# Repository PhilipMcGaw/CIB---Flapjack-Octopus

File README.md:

# CIB - Flapjack Octopus
<div align="center">

<!-- removed as not used in this repo  -->

</div>

|  | Breakout board for Labjack T7 |
| ------------- |:-------------:|

Breakout board for Labjack T7

### Flapjack Octopus -- Labjack T7 Breakout

This is a breakout PCB for a Labjack T7, with 2.5 mm pitch screw headers to allow for quick wiring to the breakout PCB.

  * Digital IO ports are 5 V tolerant, there is no additional protection on the PCB.
  * Digital IO on ports C, E, F and M each have an LED that illuminates when 5V DC is applied
  * Digital IO port F is also set up as eight relay outputs, allowing up to eight 12/24 V (separate power supply required) to be driven from the T7 Labjack
  * Analogue in ports are taken via a potential divider to allow pre-scaling if required.
  * Additional terminals are available for 5V and Ground, as well as other pins, these are on the lower edge.

# Sub Modules

github.com/PhilipMcGaw/common_kicad

git submodule add https://github.com/PhilipMcGaw/common_kicad KiCAD/Common

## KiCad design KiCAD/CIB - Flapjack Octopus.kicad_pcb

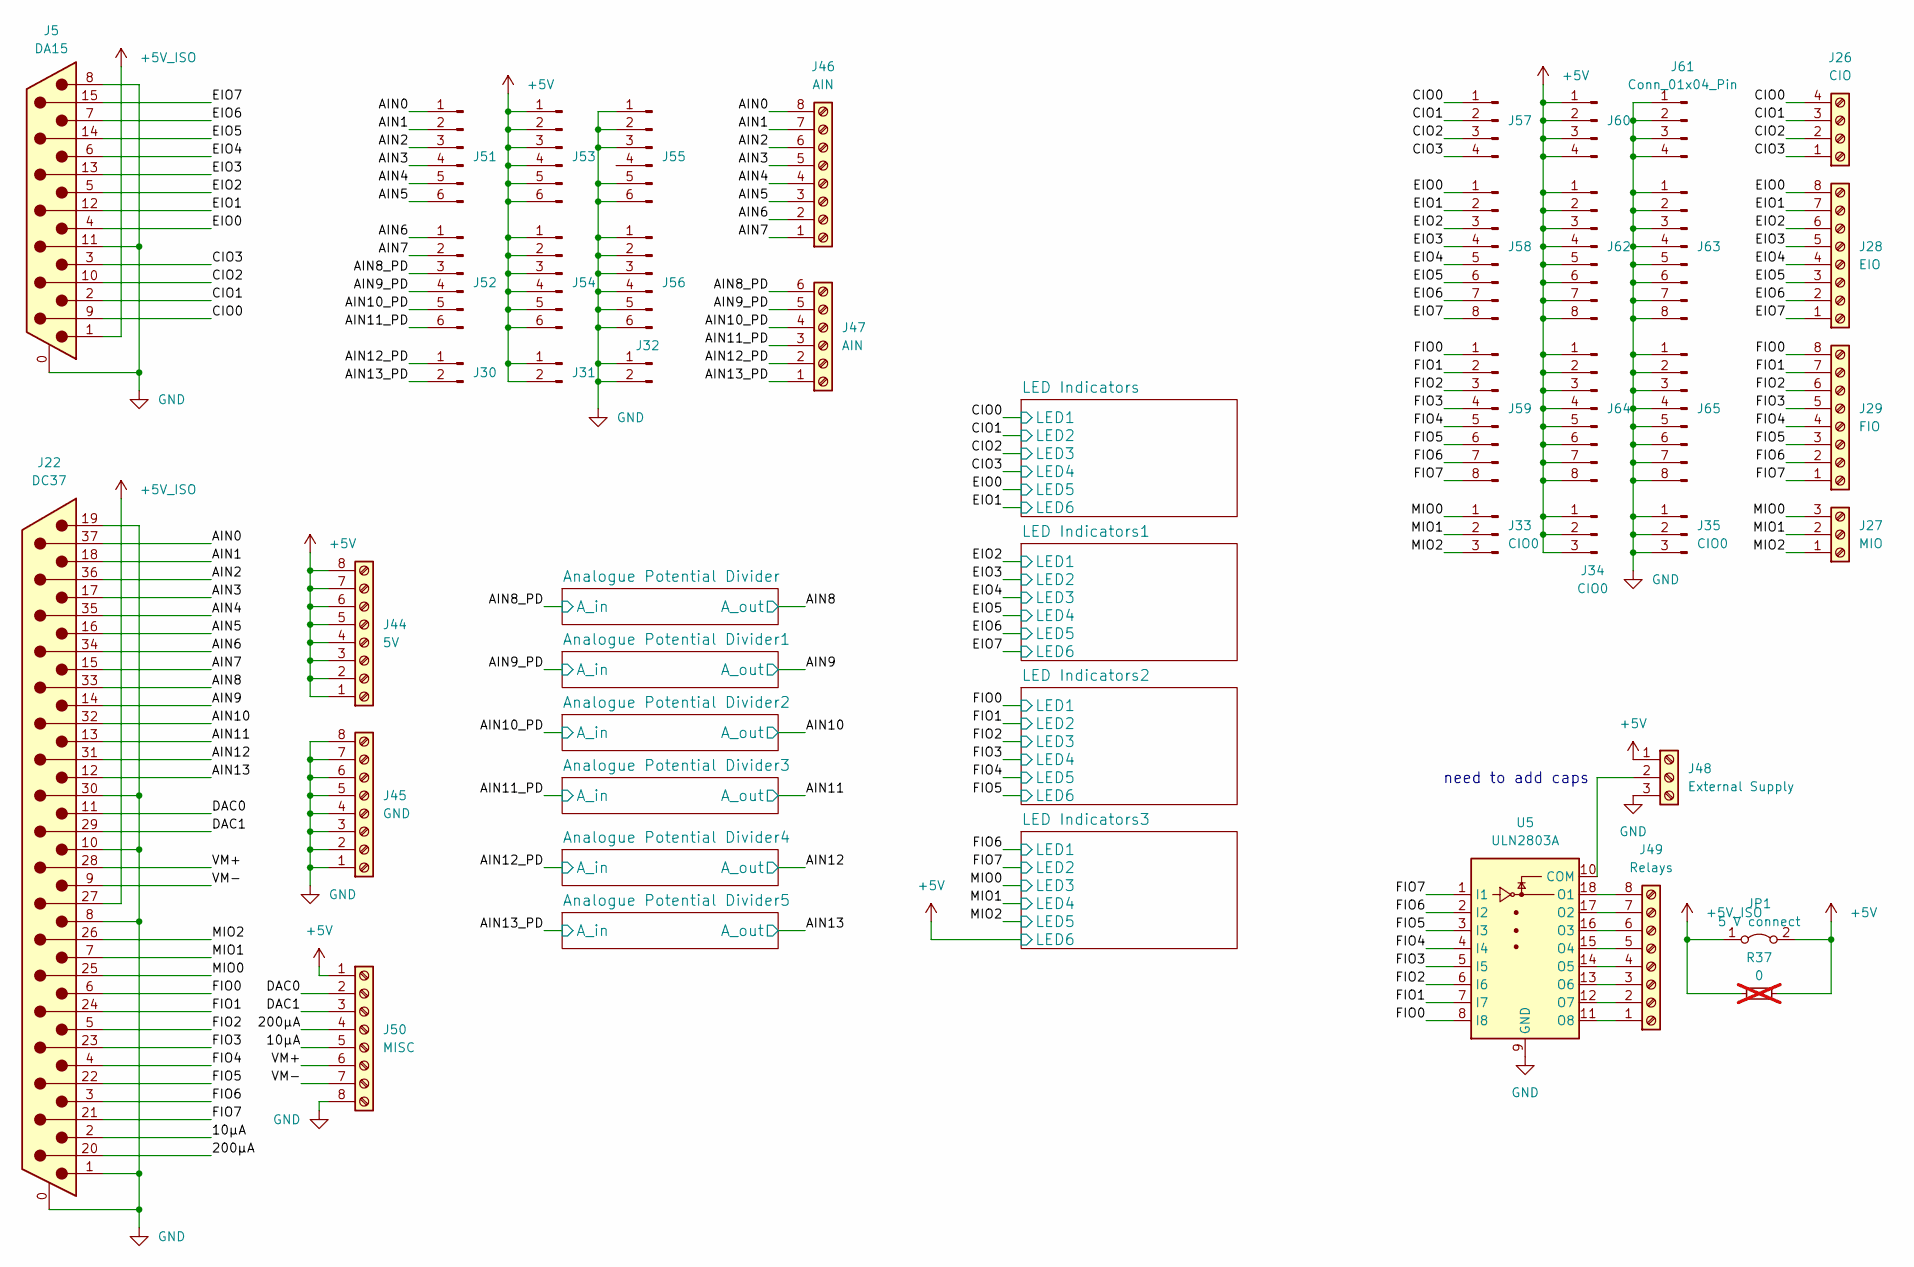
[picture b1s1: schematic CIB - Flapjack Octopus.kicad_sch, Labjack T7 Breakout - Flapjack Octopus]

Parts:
J5: DA15; DSUB-15_Male_Horizontal_P2.77x2.84mm_EdgePinOffset9.90mm_Ho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
J22: DC37; DSUB-37_Male_Horizontal_P2.77x2.84mm_EdgePinOffset7.70mm_Ho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
J26: CIO; TerminalBlock_Phoenix_MPT-0,5-4-2.54_1x04_P2.54mm_Horizontal
J27: MIO; TerminalBlock_Phoenix_MPT-0,5-3-2.54_1x03_P2.54mm_Horizontal
J28: EIO; TerminalBlock_Phoenix_MPT-0,5-8-2.54_1x08_P2.54mm_Horizontal
J29: FIO; TerminalBlock_Phoenix_MPT-0,5-8-2.54_1x08_P2.54mm_Horizontal
J30, J31, J32: Conn_01x02_Pin; PinSocket_1x02_P2.54mm_Vertical
J33, J34, J35: CIO0; PinSocket_1x03_P2.54mm_Vertical
J44: 5V; TerminalBlock_Phoenix_MPT-0,5-8-2.54_1x08_P2.54mm_Horizontal
J45: GND; TerminalBlock_Phoenix_MPT-0,5-8-2.54_1x08_P2.54mm_Horizontal
J46: AIN; TerminalBlock_Phoenix_MPT-0,5-8-2.54_1x08_P2.54mm_Horizontal
J47: AIN; TerminalBlock_Phoenix_MPT-0,5-6-2.54_1x06_P2.54mm_Horizontal
J48: External Supply; TerminalBlock_Phoenix_MPT-0,5-3-2.54_1x03_P2.54mm_Horizontal
J49: Relays; TerminalBlock_Phoenix_MPT-0,5-8-2.54_1x08_P2.54mm_Horizontal
J50: MISC; TerminalBlock_Phoenix_MPT-0,5-8-2.54_1x08_P2.54mm_Horizontal
J51, J52, J53, J54, J55, J56: Conn_01x06_Pin; PinHeader_1x06_P2.54mm_Vertical
J57, J60, J61: Conn_01x04_Pin; PinHeader_1x04_P2.54mm_Vertical
J58, J59, J62, J63, J64, J65: Conn_01x08_Pin; PinHeader_1x08_P2.54mm_Vertical
JP1: 5 V connect; SolderJumper-2_P1.3mm_Bridged_Pad1.0x1.5mm
R37: 0; R_0805_2012Metric_Pad1.20x1.40mm_HandSolder; not fitted
U5: ULN2803A; SOIC-18W_7.5x11.6mm_P1.27mm

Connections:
+5V: J31.1, J31.2, J34.1, J34.2, J34.3, J44.1, J44.2, J44.3, J44.4, J44.5, J44.6, J44.7, J44.8, J48.1, J50.1, J53.1, J53.2, J53.3, J53.4, J53.5, J53.6, J54.1, J54.2, J54.3, J54.4, J54.5, J54.6, J60.1, J60.2, J60.3, J60.4, J62.1, J62.2, J62.3, J62.4, J62.5, J62.6, J62.7, J62.8, J64.1, J64.2, J64.3, J64.4, J64.5, J64.6, J64.7, J64.8, JP1.2 (B), R37.2; also elsewhere on the board
+5V_ISO: J5.1, J22.27, JP1.1 (A), R37.1
/10µA: J22.2, J50.5
/200µA: J22.20, J50.4
/AIN0: J22.37, J46.8, J51.1
/AIN1: J22.18, J46.7, J51.2
/AIN2: J22.36, J46.6, J51.3
/AIN3: J22.17, J46.5, J51.4
/AIN4: J22.35, J46.4, J51.5
/AIN5: J22.16, J46.3, J51.6
/AIN6: J22.34, J46.2, J52.1
/AIN7: J22.15, J46.1, J52.2
/AIN8: J22.33; also elsewhere on the board
/AIN8_PD: J47.6, J52.3; also elsewhere on the board
/AIN9: J22.14; also elsewhere on the board
/AIN9_PD: J47.5, J52.4; also elsewhere on the board
/AIN10: J22.32; also elsewhere on the board
/AIN10_PD: J47.4, J52.5; also elsewhere on the board
/AIN11: J22.13; also elsewhere on the board
/AIN11_PD: J47.3, J52.6; also elsewhere on the board
/AIN12: J22.31; also elsewhere on the board
/AIN12_PD: J30.1, J47.2; also elsewhere on the board
/AIN13: J22.12; also elsewhere on the board
/AIN13_PD: J30.2, J47.1; also elsewhere on the board
/CIO0: J5.9, J26.4, J57.1; also elsewhere on the board
/CIO1: J5.2, J26.3, J57.2; also elsewhere on the board
/CIO2: J5.10, J26.2, J57.3; also elsewhere on the board
/CIO3: J5.3, J26.1, J57.4; also elsewhere on the board
/DAC0: J22.11, J50.2
/DAC1: J22.29, J50.3
/EIO0: J5.4, J28.8, J58.1; also elsewhere on the board
/EIO1: J5.12, J28.7, J58.2; also elsewhere on the board
/EIO2: J5.5, J28.6, J58.3; also elsewhere on the board
/EIO3: J5.13, J28.5, J58.4; also elsewhere on the board
/EIO4: J5.6, J28.4, J58.5; also elsewhere on the board
/EIO5: J5.14, J28.3, J58.6; also elsewhere on the board
/EIO6: J5.7, J28.2, J58.7; also elsewhere on the board
/EIO7: J5.15, J28.1, J58.8; also elsewhere on the board
/FIO0: J22.6, J29.8, J59.1, U5.8 (I8); also elsewhere on the board
/FIO1: J22.24, J29.7, J59.2, U5.7 (I7); also elsewhere on the board
/FIO2: J22.5, J29.6, J59.3, U5.6 (I6); also elsewhere on the board
/FIO3: J22.23, J29.5, J59.4, U5.5 (I5); also elsewhere on the board
/FIO4: J22.4, J29.4, J59.5, U5.4 (I4); also elsewhere on the board
/FIO5: J22.22, J29.3, J59.6, U5.3 (I3); also elsewhere on the board
/FIO6: J22.3, J29.2, J59.7, U5.2 (I2); also elsewhere on the board
/FIO7: J22.21, J29.1, J59.8, U5.1 (I1); also elsewhere on the board
/MIO0: J22.25, J27.3, J33.1; also elsewhere on the board
/MIO1: J22.7, J27.2, J33.2; also elsewhere on the board
/MIO2: J22.26, J27.1, J33.3; also elsewhere on the board
/VM+: J22.28, J50.6
/VM-: J22.9, J50.7
GND: J5.0 (PAD), J5.8, J5.11 (P111), J22.0 (PAD), J22.1, J22.8, J22.10, J22.19, J22.30, J32.1, J32.2, J35.1, J35.2, J35.3, J45.1, J45.2, J45.3, J45.4, J45.5, J45.6, J45.7, J45.8, J48.3, J50.8, J55.1, J55.2, J55.3, J55.5, J55.6, J56.1, J56.2, J56.3, J56.4, J56.5, J56.6, J61.1, J61.2, J61.3, J61.4, J63.1, J63.2, J63.3, J63.4, J63.5, J63.6, J63.7, J63.8, J65.1, J65.2, J65.3, J65.4, J65.5, J65.6, J65.7, J65.8, U5.9 (GND); also elsewhere on the board
unnamed: J48.2, U5.10 (COM)
unnamed: J49.1, U5.11 (O8)
unnamed: J49.2, U5.12 (O7)
unnamed: J49.3, U5.13 (O6)
unnamed: J49.4, U5.14 (O5)
unnamed: J49.5, U5.15 (O4)
unnamed: J49.6, U5.16 (O3)
unnamed: J49.7, U5.17 (O2)
unnamed: J49.8, U5.18 (O1)

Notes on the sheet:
need to add caps

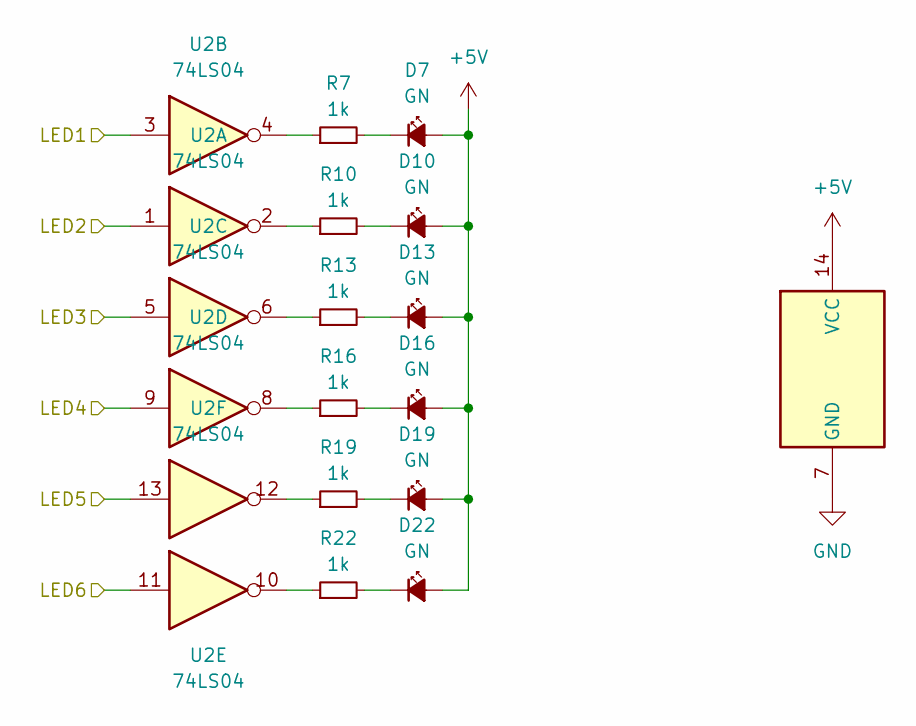
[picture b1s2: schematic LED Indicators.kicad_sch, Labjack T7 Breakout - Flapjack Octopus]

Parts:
D7, D10, D13, D16, D19, D22: GN; LED_0805_2012Metric_Pad1.15x1.40mm_HandSolder
R7, R10, R13, R16, R19, R22: 1k; R_0805_2012Metric_Pad1.20x1.40mm_HandSolder
U2, U4: 74LS04

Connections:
+5V: D7.2 (A), D10.2 (A), D13.2 (A), D16.2 (A), D19.2 (A), D22.2 (A), U4.14 (VCC); also elsewhere on the board
/CIO0: U2.3; also elsewhere on the board
/CIO1: U2.1; also elsewhere on the board
/CIO2: U2.5; also elsewhere on the board
/CIO3: U2.9; also elsewhere on the board
/EIO0: U2.13; also elsewhere on the board
/EIO1: U2.11; also elsewhere on the board
/FIO0: U4.3; also elsewhere on the board
/FIO1: U4.1; also elsewhere on the board
/FIO2: U4.5; also elsewhere on the board
/FIO3: U4.9; also elsewhere on the board
/FIO4: U4.13; also elsewhere on the board
/FIO5: U4.11; also elsewhere on the board
GND: U4.7 (GND); also elsewhere on the board
unnamed: D7.1 (K), R7.2
unnamed: D10.1 (K), R10.2
unnamed: D13.1 (K), R13.2
unnamed: D16.1 (K), R16.2
unnamed: D19.1 (K), R19.2
unnamed: D22.1 (K), R22.2
unnamed: R7.1, U2.4
unnamed 93: U4.4; also elsewhere on the board
unnamed: R10.1, U2.2
unnamed 96: U4.2; also elsewhere on the board
unnamed: R13.1, U2.6
unnamed 99: U4.6; also elsewhere on the board
unnamed: R16.1, U2.8
unnamed 102: U4.8; also elsewhere on the board
unnamed: R19.1, U2.12
unnamed 105: U4.12; also elsewhere on the board
unnamed: R22.1, U2.10
unnamed 108: U4.10; also elsewhere on the board

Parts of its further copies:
D8, D9, D11, D12, D14, D15, D17, D18, D20, D21, D23, D24, D25, D26, D27, D28, D29, D30: GN; LED_0805_2012Metric_Pad1.15x1.40mm_HandSolder
R8, R9, R11, R12, R14, R15, R17, R18, R20, R21, R23, R24, R25, R26, R27, R28, R29, R30: 1k; R_0805_2012Metric_Pad1.20x1.40mm_HandSolder
U3, U6: 74LS04

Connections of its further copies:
+5V: D8.2 (A), D9.2 (A), D11.2 (A), D12.2 (A), D14.2 (A), D15.2 (A), D17.2 (A), D18.2 (A), D20.2 (A), D21.2 (A), D23.2 (A), D24.2 (A), D25.2 (A), D26.2 (A), D27.2 (A), D28.2 (A), D29.2 (A), D30.2 (A), U6.11, U6.14 (VCC); also elsewhere on the board
/EIO2: U3.3; also elsewhere on the board
/EIO3: U3.1; also elsewhere on the board
/EIO4: U3.5; also elsewhere on the board
/EIO5: U3.9; also elsewhere on the board
/EIO6: U3.13; also elsewhere on the board
/EIO7: U3.11; also elsewhere on the board
/FIO6: U6.3; also elsewhere on the board
/FIO7: U6.1; also elsewhere on the board
/MIO0: U6.5; also elsewhere on the board
/MIO1: U6.9; also elsewhere on the board
/MIO2: U6.13; also elsewhere on the board
GND: U6.7 (GND); also elsewhere on the board
unnamed: D8.1 (K), R8.2
unnamed: D9.1 (K), R9.2
unnamed: D11.1 (K), R11.2
unnamed: D12.1 (K), R12.2
unnamed: D14.1 (K), R14.2
unnamed: D15.1 (K), R15.2
unnamed: D17.1 (K), R17.2
unnamed: D18.1 (K), R18.2
unnamed: D20.1 (K), R20.2
unnamed: D21.1 (K), R21.2
unnamed: D23.1 (K), R23.2
unnamed: D24.1 (K), R24.2
unnamed: D25.1 (K), R25.2
unnamed: D26.1 (K), R26.2
unnamed: D27.1 (K), R27.2
unnamed: D28.1 (K), R28.2
unnamed: D29.1 (K), R29.2
unnamed: D30.1 (K), R30.2
unnamed: R8.1, U3.4
unnamed 93: R9.1; also elsewhere on the board
unnamed: R11.1, U3.2
unnamed 96: R12.1; also elsewhere on the board
unnamed: R14.1, U3.6
unnamed 99: R15.1; also elsewhere on the board
unnamed: R17.1, U3.8
unnamed 102: R18.1; also elsewhere on the board
unnamed: R20.1, U3.12
unnamed 105: R21.1; also elsewhere on the board
unnamed: R23.1, U3.10
unnamed 108: R24.1; also elsewhere on the board
unnamed: R25.1, U6.4
unnamed: R26.1, U6.2
unnamed: R27.1, U6.6
unnamed: R28.1, U6.8
unnamed: R29.1, U6.12
unnamed: R30.1, U6.10

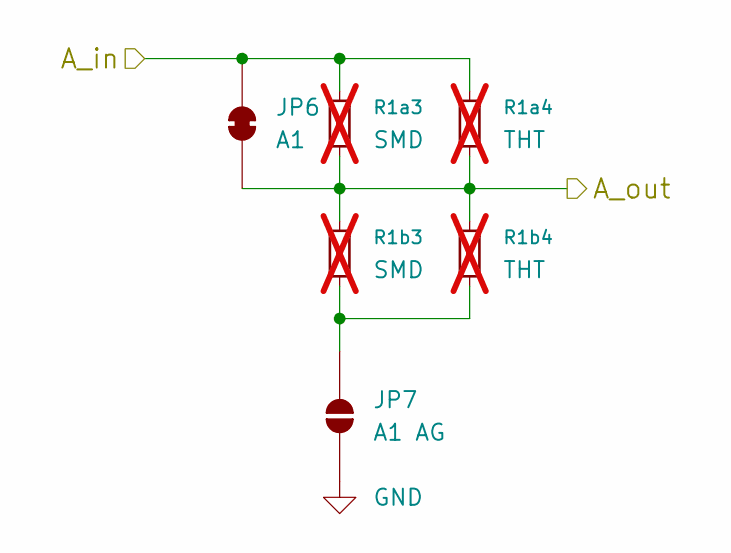
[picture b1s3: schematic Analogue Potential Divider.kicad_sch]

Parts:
JP6: A1; SolderJumper-2_P1.3mm_Bridged_RoundedPad1.0x1.5mm
JP7: A1 AG; SolderJumper-2_P1.3mm_Open_RoundedPad1.0x1.5mm
R1a3, R1b3: SMD; R_0805_2012Metric_Pad1.20x1.40mm_HandSolder; not fitted
R1a4, R1b4: THT; R_Axial_DIN0207_L6.3mm_D2.5mm_P10.16mm_Horizontal; not fitted

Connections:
/AIN8: JP6.1 (A), R1a3.2, R1a4.2, R1b3.1, R1b4.1; also elsewhere on the board
/AIN8_PD: JP6.2 (B), R1a3.1, R1a4.1; also elsewhere on the board
GND: JP7.1 (A); also elsewhere on the board
unnamed: JP7.2 (B), R1b3.2, R1b4.2

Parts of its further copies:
JP8, JP10, JP12, JP14, JP16: A1; SolderJumper-2_P1.3mm_Bridged_RoundedPad1.0x1.5mm
JP9, JP11, JP13, JP15, JP17: A1 AG; SolderJumper-2_P1.3mm_Open_RoundedPad1.0x1.5mm
R1a5, R1a7, R1a9, R1a11, R1a13, R1b5, R1b7, R1b9, R1b11, R1b13: SMD; R_0805_2012Metric_Pad1.20x1.40mm_HandSolder; not fitted
R1a6, R1a8, R1a10, R1a12, R1a14, R1b6, R1b8, R1b10, R1b12, R1b14: THT; R_Axial_DIN0207_L6.3mm_D2.5mm_P10.16mm_Horizontal; not fitted

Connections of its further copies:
/AIN9: JP8.1 (A), R1a5.2, R1a6.2, R1b5.1, R1b6.1; also elsewhere on the board
/AIN9_PD: JP8.2 (B), R1a5.1, R1a6.1; also elsewhere on the board
/AIN10: JP10.1 (A), R1a7.2, R1a8.2, R1b7.1, R1b8.1; also elsewhere on the board
/AIN10_PD: JP10.2 (B), R1a7.1, R1a8.1; also elsewhere on the board
/AIN11: JP12.1 (A), R1a9.2, R1a10.2, R1b9.1, R1b10.1; also elsewhere on the board
/AIN11_PD: JP12.2 (B), R1a9.1, R1a10.1; also elsewhere on the board
/AIN12: JP14.1 (A), R1a11.2, R1a12.2, R1b11.1, R1b12.1; also elsewhere on the board
/AIN12_PD: JP14.2 (B), R1a11.1, R1a12.1; also elsewhere on the board
/AIN13: JP16.1 (A), R1a13.2, R1a14.2, R1b13.1, R1b14.1; also elsewhere on the board
/AIN13_PD: JP16.2 (B), R1a13.1, R1a14.1; also elsewhere on the board
GND: JP9.1 (A), JP11.1 (A), JP13.1 (A), JP15.1 (A), JP17.1 (A); also elsewhere on the board
unnamed: JP9.2 (B), R1b5.2, R1b6.2
unnamed: JP11.2 (B), R1b7.2, R1b8.2
unnamed: JP13.2 (B), R1b9.2, R1b10.2
unnamed: JP15.2 (B), R1b11.2, R1b12.2
unnamed: JP17.2 (B), R1b13.2, R1b14.2

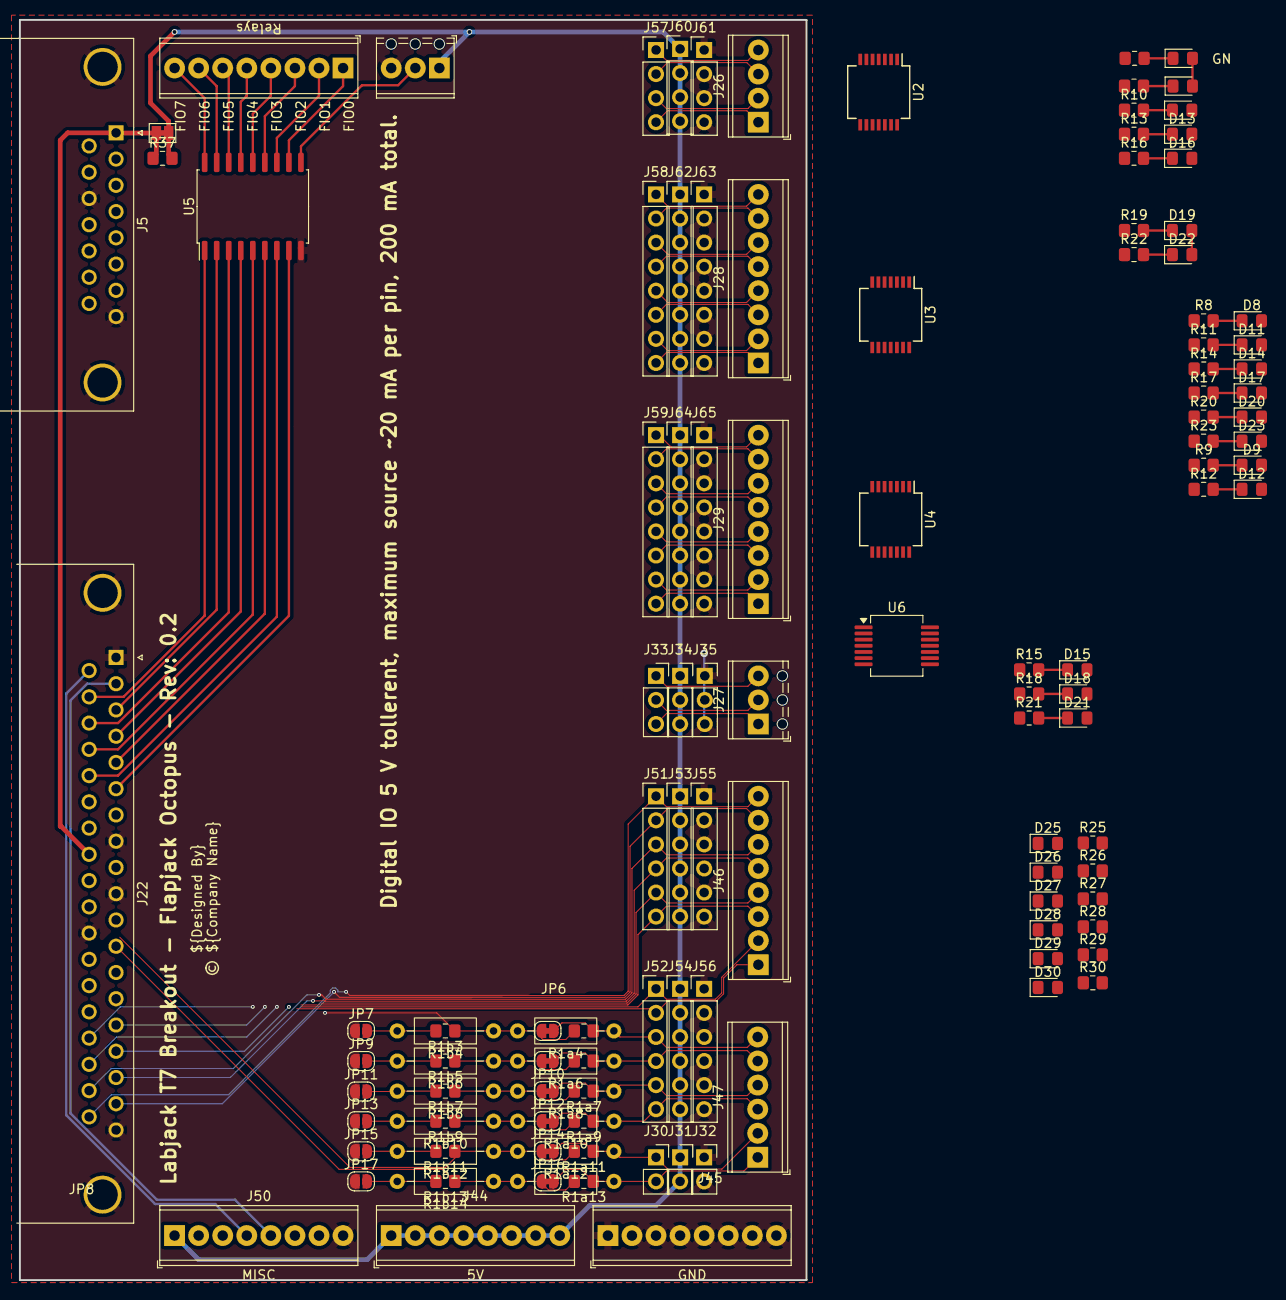
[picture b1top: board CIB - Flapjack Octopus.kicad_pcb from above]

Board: 2 copper layers, 83.0 x 133.0 mm, 125 parts (0 on the bottom side), 115 nets.

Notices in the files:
README.md:
License: CC BY-NC-SA
Hardware: CERN-OHL-S
By Ed Bowlby, NOAA/Olympic Coast NMS; NOAA/OAR/Office of Ocean Exploration - NOAA Photo Library, Public Domain
